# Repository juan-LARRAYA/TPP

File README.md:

# EPS CubeSat - Sistema de Gestión de Energía

Sistema de gestión de energía (EPS - Electric Power System) para CubeSat, diseñado para cumplir con las especificaciones requeridas en tensiones de salida, tasas de datos para comunicación con periféricos y vida útil extendida.

## Autores

- **Larraya, Juan Cruz** - 104162 - jlarraya@fi.uba.ar
- **Stirparo, Nicolás** - 105885 - nstirparo@fi.uba.ar
- **Paulino Alaya, Diego** - 104311 - dpaulino@fi.uba.ar

## Director y Codirectores

- **Director**: Enrique Jorge Castelli
- **Codirectores**:
  - Fernando Filippetti
  - Monica Viviana Nitoli

## Introducción

El EPS es uno de los subsistemas más críticos de un satélite, ya que de su correcto funcionamiento depende la operación continua de los demás módulos, tales como el sistema de comunicaciones, el control de actitud y el payload. Su rol principal es gestionar la energía captada por los paneles solares, regular y distribuir las tensiones necesarias, cargar las baterías y garantizar tanto la protección de las mismas como la seguridad de los circuitos asociados. Además, debe ser capaz de sensar parámetros eléctricos y térmicos para reportarlos al computador a bordo y así optimizar la eficiencia energética durante la misión.

## Motivación

Este proyecto surge de la escasa oferta de módulos EPS en Sudamérica y de los elevados costos de los productos disponibles en el mercado internacional, que en muchos casos carecen de documentación abierta para su integración. Ante esta situación, se plantea la oportunidad de desarrollar un sistema propio que no solo satisfaga las necesidades técnicas del CubeSat propuesto, sino que también contribuya al crecimiento de la industria espacial argentina mediante la generación de conocimiento y tecnología local.

## Objetivos

El proyecto entrega un **prototipo operativo** junto con:
- Documentación técnica completa
- Mediciones necesarias para su validación
- Circuito esquemático para realizar copias del circuito industrialmente a escala en un PCB bajo la norma PC104

## Características Técnicas

El sistema EPS desarrollado cuenta con las siguientes características:

### Diseño Modular
- **PPC (Power Processing and Control)**: Optimizado con control digital directo
- **BMS (Battery Management System)**: Sistema de gestión de baterías a medida
- **PDU (Power Distribution Unit)**: Unidad de distribución de energía eficiente

### Monitoreo y Sensado
- Bus I²C con sensores **INA219** para monitoreo preciso y escalable
- Medición de tensión, corriente y temperatura en puntos críticos del sistema
- Telemetría completa de parámetros eléctricos y térmicos

### Gestión Inteligente de Baterías (BMS)
- Protección integral contra sobre y baja tensión
- Protección contra sobrecorriente
- Monitoreo de temperatura
- Estado de carga (SOC)
- Capacidad de balanceo de celdas

### Cargador de Baterías con MPPT
- Extracción de máxima potencia de los paneles solares
- Algoritmo MPPT para optimización de eficiencia de carga
- Tres canales de entrada fotovoltaica independientes

### Regulación y Distribución de Energía
- Tres buses de alimentación regulados (3.3V, 5V)
- Redundancia en las salidas de 3.3V y 5V
- Limitadores de corriente en cada canal
- Compatibilidad con norma PC104

### Interfaz de Comunicación
- Comunicación UART/USART con la computadora a bordo del CubeSat
- Comandos y lectura de registros de estado de todos los módulos
- Bus I²C para sensores y periféricos

## Desarrollo del Proyecto

### Prototipo Final

### Fallos Encontrados y Soluciones Implementadas

Durante el desarrollo del proyecto se enfrentaron desafíos significativos que requirieron cambios en la metodología y arquitectura del sistema:

#### 1. Fallo Funcional del Primer Prototipo Monolítico

**Problema:** El diseño inicial, concebido como una solución "todo en uno" y fabricado profesionalmente, falló en las pruebas iniciales. Esto se debió a la complejidad inherente de un sistema monolítico, donde la interdependencia de los componentes dificulta la depuración y la identificación de la causa raíz de los fallos.

**Solución:** Se adoptó una metodología de desarrollo modular e incremental. El sistema EPS se descompuso en sus bloques funcionales principales (PPC, BMS, PDU), y cada módulo se implementó y probó de forma aislada utilizando prototipos de bajo costo. Esta estrategia permitió una depuración más controlada y económica.

#### 2. Ineficiencia en la Adquisición de Datos (Mapeo Directo por ADC)

**Problema:** El enfoque preliminar utilizaba divisores de tensión y amplificadores operacionales conectados directamente a las entradas ADC del microcontrolador. Esto resultaba en un alto consumo de pines, complejidad del circuito debido a la circuitería de acondicionamiento de señal para cada medición, y susceptibilidad al ruido en las largas pistas analógicas.

**Solución:** Se migró a una arquitectura de monitoreo digital y distribuida basada en el bus I²C, utilizando sensores de corriente y potencia INA219. Estos dispositivos integran un amplificador de precisión y un ADC de 12 bits, transmitiendo mediciones de forma digital. Esta solución redujo drásticamente el uso de pines del microcontrolador, simplificó la interconexión, aumentó la precisión y la robustez frente al ruido.

## Estructura del Repositorio

```
TPP/
├── firmware/                      # Código fuente del firmware
│   ├── TPP STM/                  # Firmware principal para STM32
│   └── demos/                    # Demostraciones y pruebas
│       ├── DuinoSTM32/          # Ejemplos con Arduino IDE para STM32
│       ├── STM32CubeIDE/        # Proyectos de STM32CubeIDE
│       ├── filmwareSTM32/       # Firmware de prueba STM32
│       └── pruebasMppt/         # Pruebas del algoritmo MPPT
│           ├── arduino/         # Versión Arduino
│           ├── esp32/           # Versión ESP32
│           └── bluePIlPrueba/   # Versión Blue Pill (STM32F103)
│
├── hardware/                      # Diseños de hardware
│   ├── PowerSis-V0.0/           # Versión inicial del diseño
│   └── kikads/                   # Diseños en KiCad
│       ├── PowerSis-V4.4+modFinales/  # Versión 4.4 con modificaciones finales
│       ├── PowerSis-V5.0/            # Versión 5.0 (última versión)
│       └── superados/                # Versiones anteriores superadas
│
├── utilidades/                    # Herramientas y scripts de utilidad
│
├── Info util CubeSat ENERGIA/    # Información y documentación de referencia
│
└── TPP Informe.pdf               # Informe técnico del proyecto
```

## ¿Qué puedes hacer con este proyecto?

### 1. Explorar el Diseño de Hardware
Navega a la carpeta `hardware/kikads/PowerSis-V5.0/` para encontrar:
- Esquemáticos del circuito completo
- Layout del PCB en formato PC104
- Lista de materiales (BOM)
- Archivos de fabricación (Gerbers)

### 2. Compilar y Cargar el Firmware
El firmware principal se encuentra en `firmware/TPP STM/`:
- Compatible con STM32
- Incluye implementación de BMS, MPPT y PDU
- Comunicación I²C y UART
- Drivers para sensores INA219

### 3. Probar Módulos Individuales
Utiliza los demos en `firmware/demos/` para:
- Probar el algoritmo MPPT de forma aislada
- Verificar la comunicación con el BQ (BMS IC)
- Testear PWM y control de conversores
- Desarrollar sobre diferentes plataformas (Arduino, ESP32, STM32)

### 4. Replicar el Sistema
Con la documentación incluida puedes:
- Fabricar tu propio PCB siguiendo el diseño PC104
- Ensamblar el sistema con la lista de materiales
- Cargar el firmware en un microcontrolador STM32
- Integrar el EPS en tu propio CubeSat

### 5. Modificar y Adaptar
El proyecto es completamente abierto para:
- Adaptar las tensiones de salida a tus necesidades
- Modificar los algoritmos de control
- Agregar nuevos sensores o funcionalidades
- Optimizar para diferentes perfiles de misión

## Documentación

- **Informe Técnico Completo**: `TPP Informe.pdf`
- **Información de Referencia**: Carpeta `Info util CubeSat ENERGIA/`
- **Esquemáticos**: `hardware/kikads/PowerSis-V5.0/`

## Requisitos

### Para el Hardware
- PCB fabricado según diseño PC104
- Componentes según BOM incluida
- Paneles solares compatibles
- Baterías LiPo/Li-Ion

### Para el Firmware
- STM32 (recomendado STM32F103 o superior)
- IDE: Arduino IDE con soporte STM32 o STM32CubeIDE
- Programador ST-Link V2 o compatible
- Sensores INA219 para telemetría

## Primeros Pasos

1. **Revisar la documentación**: Lee el informe técnico (`TPP Informe.pdf`)
2. **Explorar el hardware**: Abre los esquemáticos en KiCad desde `hardware/kikads/PowerSis-V5.0/`
3. **Compilar un demo**: Prueba el código MPPT desde `firmware/demos/pruebasMppt/`
4. **Cargar el firmware principal**: Desde `firmware/TPP STM/`

## Licencia

Este proyecto se desarrolla como Trabajo Práctico Profesional de la Facultad de Ingeniería - UBA, con el objetivo de contribuir al desarrollo de la tecnología espacial argentina.

## Contacto

Para consultas sobre el proyecto, contactar a los autores a través de sus correos electrónicos listados arriba.

---

**Universidad de Buenos Aires - Facultad de Ingeniería**
*Trabajo Práctico Profesional - 2024*

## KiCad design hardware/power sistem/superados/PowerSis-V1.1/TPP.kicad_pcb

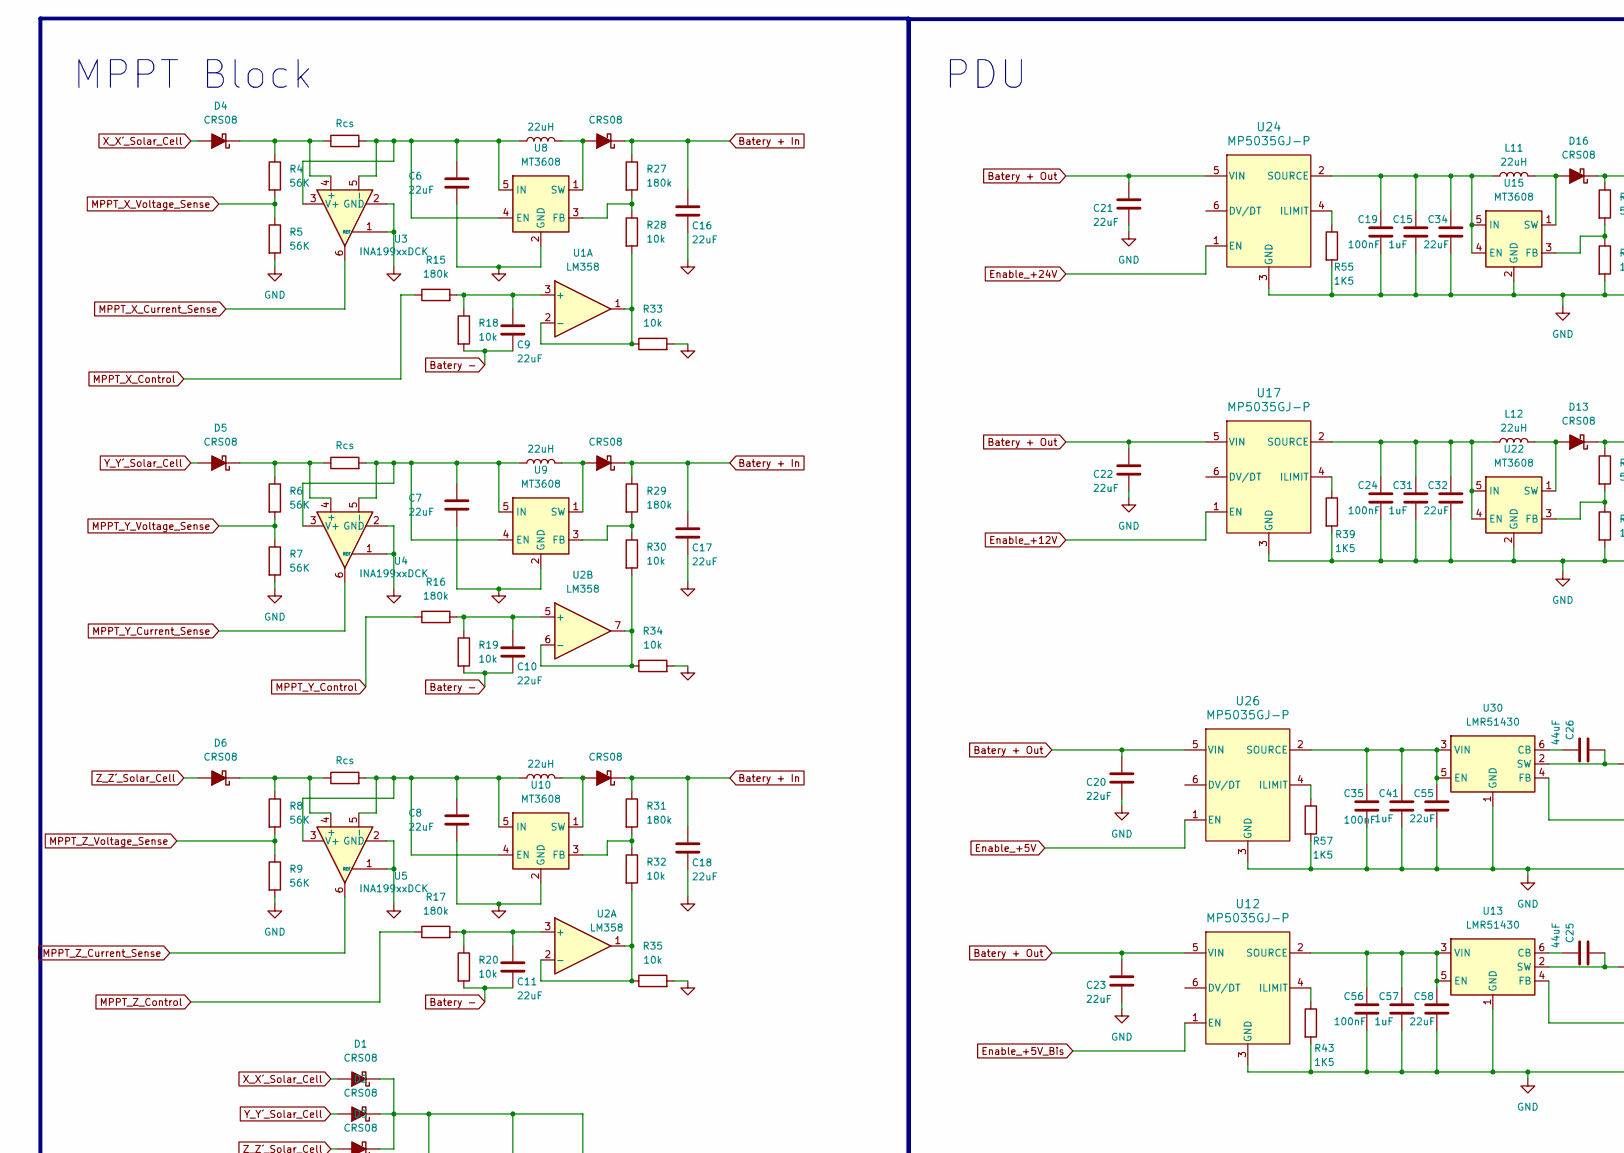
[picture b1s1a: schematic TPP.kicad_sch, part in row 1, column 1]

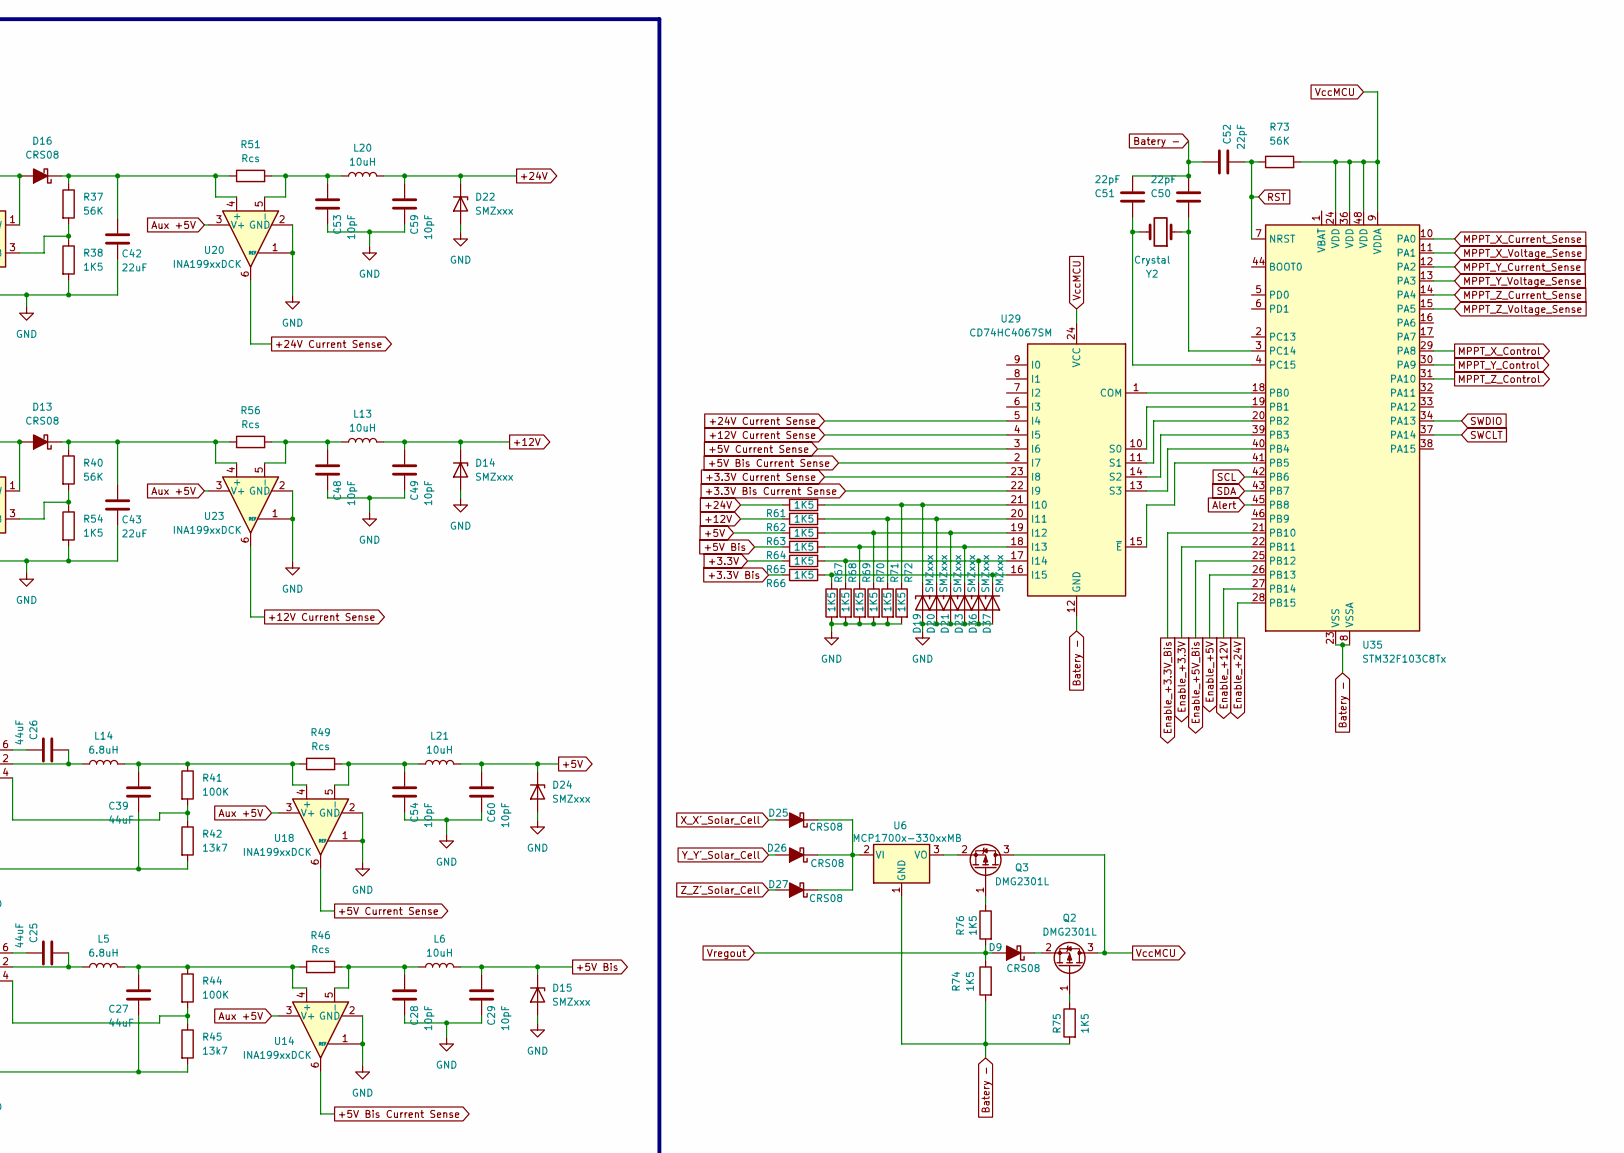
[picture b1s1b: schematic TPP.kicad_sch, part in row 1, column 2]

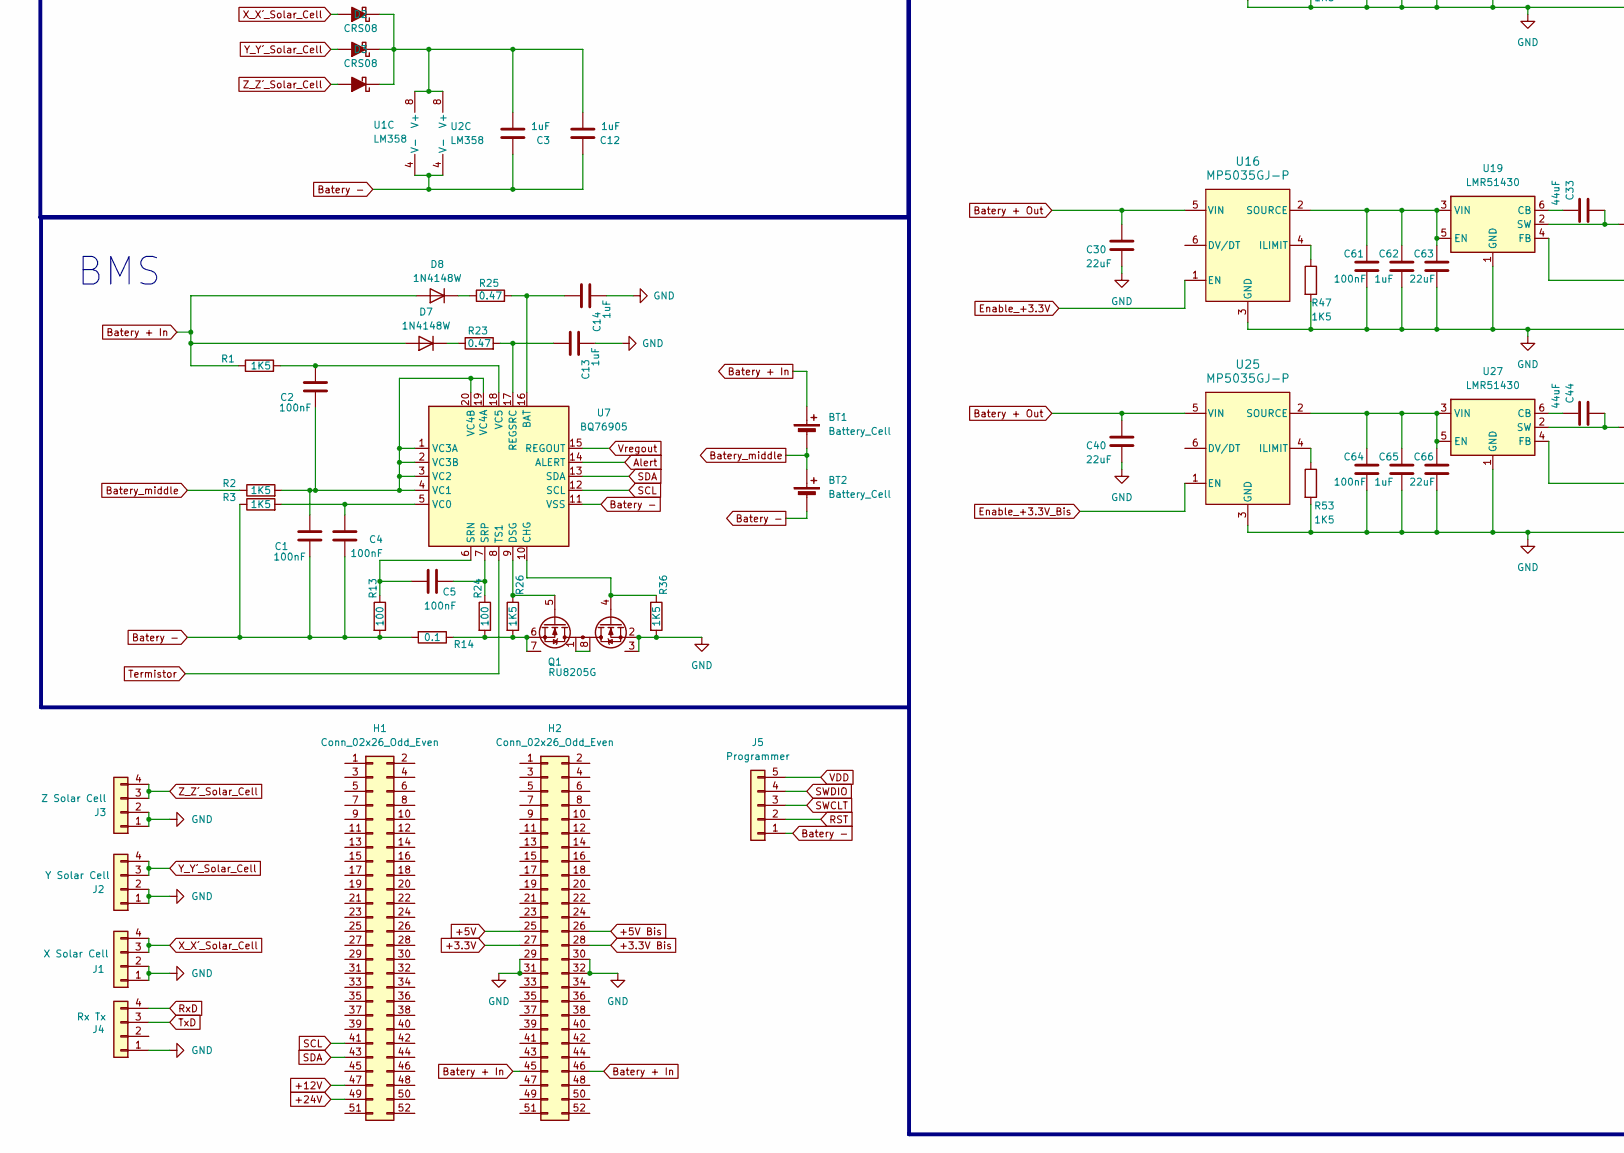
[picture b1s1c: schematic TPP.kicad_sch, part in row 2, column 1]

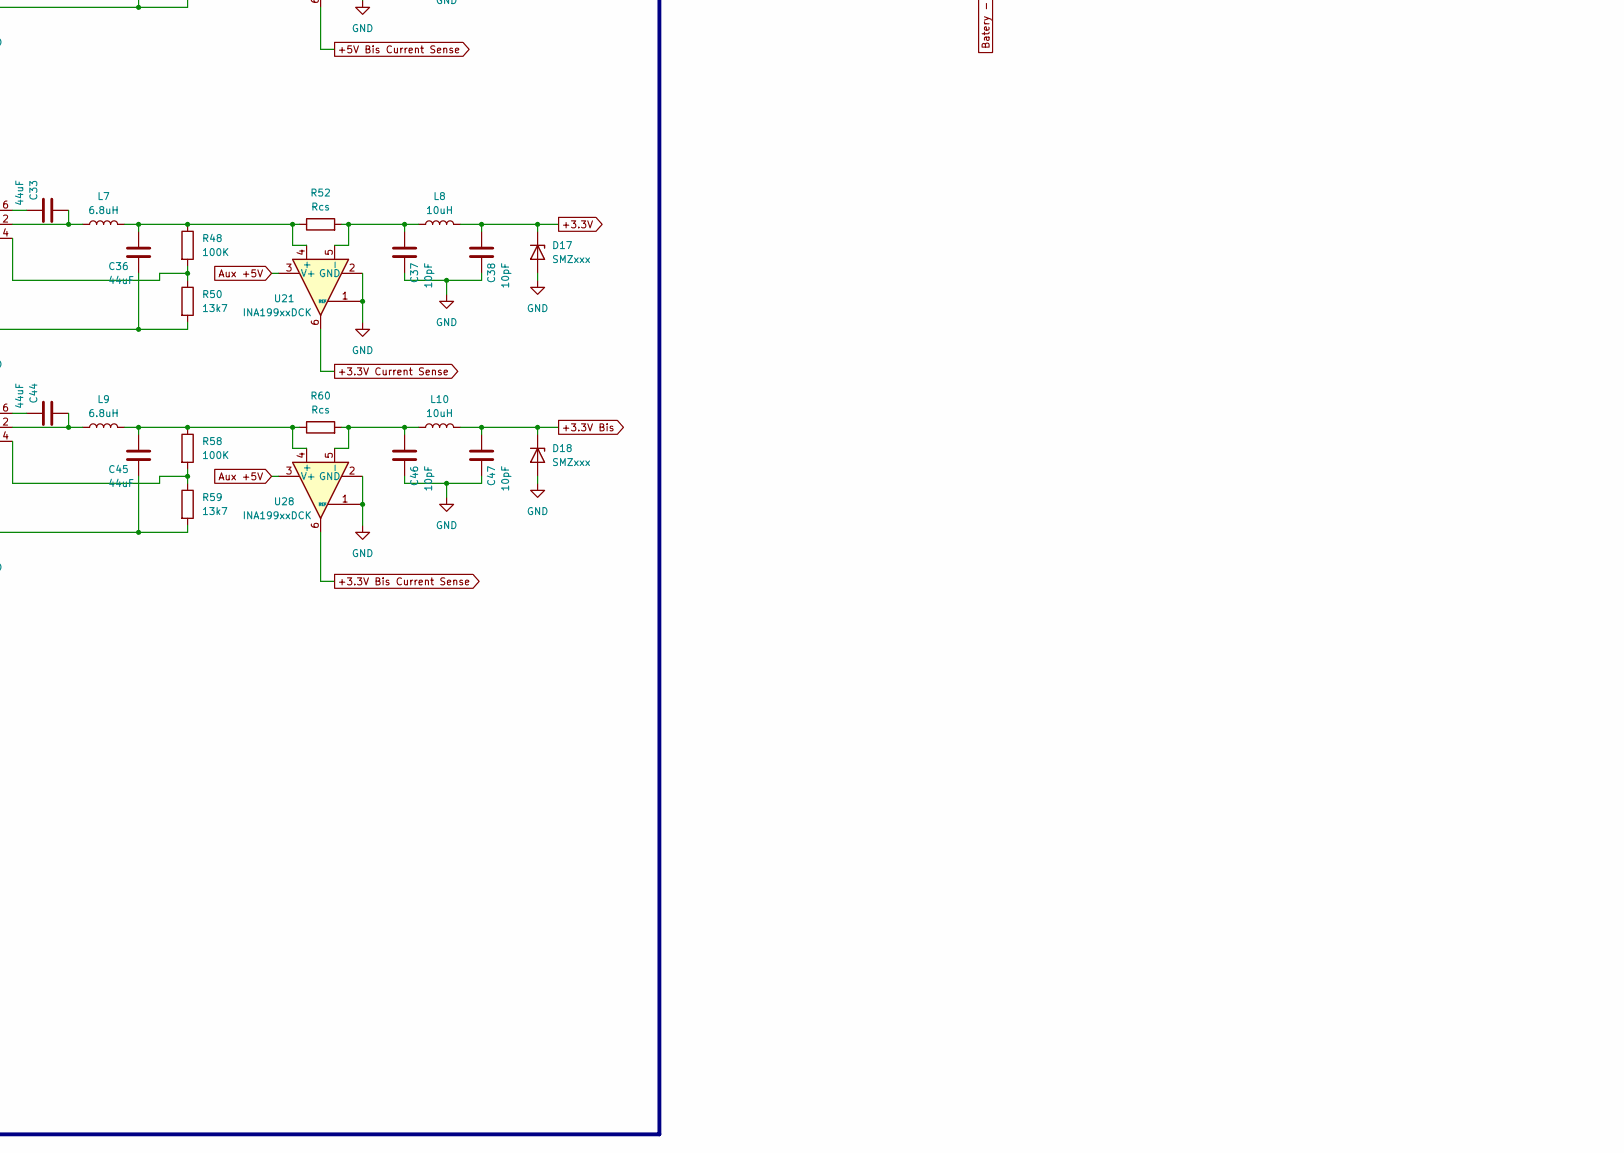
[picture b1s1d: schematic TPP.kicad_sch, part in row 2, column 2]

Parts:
BT1, BT2: Battery_Cell; BatteryHolder_MPD_BH-18650-PC2
C1, C2, C4, C5, C19, C24, C35, C56, C61, C64: 100nF; C_0603_1608Metric_Pad1.08x0.95mm_HandSolder
C3, C12, C13, C14, C15, C31, C41, C57, C62, C65: 1uF; C_0603_1608Metric_Pad1.08x0.95mm_HandSolder
C6, C7, C8, C9, C10, C11, C16, C17, C18, C20, C21, C22, C23, C30, C32, C34, C40, C42, C43, C55, C58, C63, C66: 22uF; C_0603_1608Metric_Pad1.08x0.95mm_HandSolder
C25, C26, C27, C33, C36, C39, C44, C45: 44uF; C_0603_1608Metric_Pad1.08x0.95mm_HandSolder
C28, C29, C37, C38, C46, C47, C48, C49, C53, C54, C59, C60: 10pF; C_0603_1608Metric_Pad1.08x0.95mm_HandSolder
C50, C51, C52: 22pF; C_0603_1608Metric_Pad1.08x0.95mm_HandSolder
D1, D2, D3, D4, D5, D6, D9, D10, D11, D12, D13, D16, D25, D26, D27: CRS08; D_SMA
D7, D8: 1N4148W; D_SOD-123
D14, D15, D17, D18, D19, D20, D21, D22, D23, D24, D36, D37: SMZxxx; D_MELF
H1, H2: Conn_02x26_Odd_Even; PinSocket_2x26_P2.54mm_Vertical
J1: X Solar Cell; JST_XH_S4B-XH-A-1_1x04_P2.50mm_Horizontal
J2: Y Solar Cell; JST_XH_S4B-XH-A-1_1x04_P2.50mm_Horizontal
J3: Z Solar Cell; JST_XH_S4B-XH-A-1_1x04_P2.50mm_Horizontal
J4: Rx Tx; JST_XH_S4B-XH-A-1_1x04_P2.50mm_Horizontal
J5: Programmer; PinHeader_1x05_P2.54mm_Vertical
L2, L3, L4, L11, L12: 22uH; L_Abracon_ASPI-0630LR
L5, L7, L9, L14: 6.8uH; L_Abracon_ASPI-0630LR
L6, L8, L10, L13, L20, L21: 10uH; L_Abracon_ASPI-0630LR
Q1: RU8205G; TSSOP-8_4.4x3mm_P0.65mm
Q2, Q3: DMG2301L; SOT-23
R1, R2, R3, R26, R36, R38, R39, R43, R47, R53, R54, R55, R57, R61, R62, R63, R64, R65, R66, R67, R68, R69, R70, R71, R72, R74, R75, R76: 1K5; R_0805_2012Metric_Pad1.20x1.40mm_HandSolder
R4, R5, R6, R7, R8, R9, R37, R40, R73: 56K; R_0805_2012Metric_Pad1.20x1.40mm_HandSolder
R10, R11, R12, R46, R49, R51, R52, R56, R60: Rcs; R_0805_2012Metric_Pad1.20x1.40mm_HandSolder
R13, R24: 100; R_0805_2012Metric_Pad1.20x1.40mm_HandSolder
R14: 0.1; R_0805_2012Metric_Pad1.20x1.40mm_HandSolder
R15, R16, R17, R27, R29, R31: 180k; R_0805_2012Metric_Pad1.20x1.40mm_HandSolder
R18, R19, R20, R28, R30, R32, R33, R34, R35: 10k; R_0805_2012Metric_Pad1.20x1.40mm_HandSolder
R23, R25: 0.47; R_0805_2012Metric_Pad1.20x1.40mm_HandSolder
R41, R44, R48, R58: 100K; R_0805_2012Metric_Pad1.20x1.40mm_HandSolder
R42, R45, R50, R59: 13k7; R_0805_2012Metric_Pad1.20x1.40mm_HandSolder
U1: LM358; SOIC-8_3.9x4.9mm_P1.27mm
U2: LM358
U3, U4, U5, U14, U18, U20, U21, U23, U28: INA199xxDCK; SOT-363_SC-70-6
U6: MCP1700x-330xxMB; SOT-89-3
U7: BQ76905; QFN-20-1EP_3x3mm_P0.4mm_EP1.65x1.65mm_ThermalVias
U8, U9, U10, U15, U22: MT3608; SOT-23-6
U12, U16, U17, U24, U25, U26: MP5035GJ-P; TSOT-23-6_HandSoldering
U13, U19, U27, U30: LMR51430; SOT-23-6
U29: CD74HC4067SM; SSOP-24_5.3x8.2mm_P0.65mm
U35: STM32F103C8Tx; LQFP-48_7x7mm_P0.5mm
Y2: Crystal; Crystal_HC49-U_Vertical

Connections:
+3.3V: C38.2, D17.1 (K), H2.27, L8.2
+3.3V: R65.1
+3.3V Bis: R66.1
+3.3V Bis: C47.2, D18.1 (K), H2.28, L10.2
+3.3V Bis Current Sense: U28.6, U29.22 (I9)
+3.3V Current Sense: U21.6, U29.23 (I8)
+5V: C60.2, D24.1 (K), H2.25, L21.2, R63.1
+5V Bis: C29.2, D15.1 (K), H2.26, L6.2, R64.1
+5V Bis Current Sense: U14.6, U29.2 (I7)
+5V Current Sense: U18.6, U29.3 (I6)
+12V: C49.2, D14.1 (K), H1.47, L13.2, R62.1
+12V Current Sense: U23.6, U29.4 (I5)
+24V: C59.2, D22.1 (K), H1.49, L20.2, R61.1
+24V Current Sense: U20.6, U29.5 (I4)
Alert: U7.14 (ALERT), U35.45 (PB8)
Aux +5V: U14.3 (V+), U18.3 (V+), U20.3 (V+), U21.3 (V+), U23.3 (V+), U28.3 (V+)
Batery + In: BT1.1 (+), C16.1, C17.1, C18.1, D7.2 (A), D8.2 (A), D10.1 (K), D11.1 (K), D12.1 (K), H2.45, H2.46, R1.1, R27.1, R29.1, R31.1
Batery + Out: C20.1, C21.1, C22.1, C23.1, C30.1, C40.1, U12.5 (VIN), U16.5 (VIN), U17.5 (VIN), U24.5 (VIN), U25.5 (VIN), U26.5 (VIN)
Batery -: BT2.2 (-), C1.1, C3.1, C4.1, C9.2, C10.2, C11.2, C12.1, C50.1, C51.1, C52.2, J5.1, R3.1, R13.2, R14.2, R18.2, R19.2, R20.2, R74.2, R75.2, U1.4 (V-), U2.4 (V-), U6.1 (GND), U7.11 (VSS), U29.12 (GND), U35.8 (VSSA), U35.23 (VSS), U35.35 (VSS), U35.47 (VSS)
Batery_middle: BT1.2 (-), BT2.1 (+), R2.1
Enable_+3.3V: U16.1 (EN), U35.22 (PB11)
Enable_+3.3V_Bis: U25.1 (EN), U35.21 (PB10)
Enable_+5V: U26.1 (EN), U35.26 (PB13)
Enable_+5V_Bis: U12.1 (EN), U35.25 (PB12)
Enable_+12V: U17.1 (EN), U35.27 (PB14)
Enable_+24V: U24.1 (EN), U35.28 (PB15)
GND: C6.2, C7.2, C8.2, C13.1, C14.1, C15.2, C16.2, C17.2, C18.2, C19.2, C20.2, C21.2, C22.2, C23.2, C24.2, C27.2, C28.1, C29.1, C30.2, C31.2, C32.2, C34.2, C35.2, C36.2, C37.1, C38.1, C39.2, C40.2, C41.2, C42.2, C43.2, C45.2, C46.1, C47.1, C48.1, C49.1, C53.1, C54.1, C55.2, C56.2, C57.2, C58.2, C59.1, C60.1, C61.2, C62.2, C63.2, C64.2, C65.2, C66.2, D14.2 (A), D15.2 (A), D17.2 (A), D18.2 (A), D19.2 (A), D20.2 (A), D21.2 (A), D22.2 (A), D23.2 (A), D24.2 (A), D36.2 (A), D37.2 (A), H2.29, H2.30, H2.31, H2.32, J1.1, J1.2, J2.1, J2.2, J3.1, J3.2, J4.1, Q1.2 (D1), Q1.3 (D1), R5.2, R7.2, R9.2, R33.2, R34.2, R35.2, R36.2, R38.2, R39.2, R42.2, R43.2, R45.2, R47.2, R50.2, R53.2, R54.2, R55.2, R57.2, R59.2, R67.2, R68.2, R69.2, R70.2, R71.2, R72.2, U3.1 (REF), U3.2 (GND), U4.1 (REF), U4.2 (GND), U5.1 (REF), U5.2 (GND), U8.2 (GND), U9.2 (GND), U10.2 (GND), U12.3 (GND), U13.1 (GND), U14.1 (REF), U14.2 (GND), U15.2 (GND), U16.3 (GND), U17.3 (GND), U18.1 (REF), U18.2 (GND), U19.1 (GND), U20.1 (REF), U20.2 (GND), U21.1 (REF), U21.2 (GND), U22.2 (GND), U23.1 (REF), U23.2 (GND), U24.3 (GND), U25.3 (GND), U26.3 (GND), U27.1 (GND), U28.1 (REF), U28.2 (GND), U30.1 (GND)
MPPT_X_Control: R15.1, U35.29 (PA8)
MPPT_X_Current_Sense: U3.6, U35.10 (PA0)
MPPT_X_Voltage_Sense: R4.2, R5.1, U35.11 (PA1)
MPPT_Y_Control: R16.1, U35.30 (PA9)
MPPT_Y_Current_Sense: U4.6, U35.12 (PA2)
MPPT_Y_Voltage_Sense: R6.2, R7.1, U35.13 (PA3)
MPPT_Z_Control: R17.1, U35.31 (PA10)
MPPT_Z_Current_Sense: U5.6, U35.14 (PA4)
MPPT_Z_Voltage_Sense: R8.2, R9.1, U35.15 (PA5)
unnamed: C3.2, C12.2, D1.1 (K), D2.1 (K), D3.1 (K), U1.8 (V+), U2.8 (V+)
unnamed: D4.1 (K), R4.1, R10.1, U3.4 (+)
unnamed: D5.1 (K), R6.1, R11.1, U4.4 (+)
unnamed: D6.1 (K), R8.1, R12.1, U5.4 (+)
unnamed: D7.1 (K), R23.1
unnamed: D8.1 (K), R25.1
unnamed: D9.1 (K), Q2.2 (S)
unnamed: D10.2 (A), L2.2, U8.1 (SW)
unnamed: D11.2 (A), L3.2, U9.1 (SW)
unnamed: D12.2 (A), L4.2, U10.1 (SW)
unnamed: D13.2 (A), L12.2, U22.1 (SW)
unnamed: C43.1, D13.1 (K), R40.1, R56.1, U23.4 (+)
unnamed: D16.2 (A), L11.2, U15.1 (SW)
unnamed: C42.1, D16.1 (K), R37.1, R51.1, U20.4 (+)
unnamed: D19.1 (K), R61.2, R72.1, U29.21 (I10)
unnamed: D20.1 (K), R62.2, R71.1, U29.20 (I11)
unnamed: D21.1 (K), R63.2, R70.1, U29.19 (I12)
unnamed: D23.1 (K), R64.2, R69.1, U29.18 (I13)
unnamed: D25.1 (K), D26.1 (K), D27.1 (K), U6.2 (VI)
unnamed: D36.1 (K), R65.2, R68.1, U29.17 (I14)
unnamed: D37.1 (K), R66.2, R67.1, U29.16 (I15)
unnamed: Q1.4 (G1), R36.1, U7.10 (CHG)
unnamed: Q1.5 (G2), R26.1, U7.9 (DSG)
unnamed: Q1.1 (S1/D2), Q1.8 (S1/D2)
unnamed: Q1.6 (S2), Q1.7 (S2), R14.1, R24.2, R26.2
unnamed: Q2.1 (G), R75.1
unnamed: Q3.1 (G), R76.1
unnamed: Q3.2 (S), U6.3 (VO)
unnamed: C9.1, R15.2, R18.1, U1.3 (+)
unnamed: R28.2, R33.1, U1.1, U1.2 (-)
unnamed: C11.1, R17.2, R20.1, U2.3 (+)
unnamed: R32.2, R35.1, U2.1, U2.2 (-)
unnamed: C10.1, R16.2, R19.1, U2.5 (+)
unnamed: R30.2, R34.1, U2.6 (-), U2.7
unnamed: C6.1, L2.1, R10.2, U3.3 (V+), U3.5 (-), U8.4 (EN), U8.5 (IN)
unnamed: C7.1, L3.1, R11.2, U4.3 (V+), U4.5 (-), U9.4 (EN), U9.5 (IN)
unnamed: C14.2, R25.2, U7.16 (BAT)
unnamed: C13.2, R23.2, U7.17 (REGSRC)
unnamed: C5.1, R13.1, U7.6 (SRN)
unnamed: C5.2, R24.1, U7.7 (SRP)
unnamed: C4.2, R3.2, U7.5 (VC0)
unnamed: C1.2, C2.1, R2.2, U7.1 (VC3A), U7.2 (VC3B), U7.3 (VC2), U7.4 (VC1), U7.19 (VC4A), U7.20 (VC4B)
unnamed: C2.2, R1.2, U7.18 (VC5)
unnamed: R27.2, R28.1, U8.3 (FB)
unnamed: R29.2, R30.1, U9.3 (FB)
unnamed: C8.1, L4.1, R12.2, U5.3 (V+), U5.5 (-), U10.4 (EN), U10.5 (IN)
unnamed: R31.2, R32.1, U10.3 (FB)
unnamed: R43.1, U12.4 (ILIMIT)
unnamed: C56.1, C57.1, C58.1, U12.2 (SOURCE), U13.3 (VIN), U13.5 (EN)
unnamed: C25.2, U13.6 (CB)
unnamed: R44.2, R45.1, U13.4 (FB)
unnamed: C25.1, L5.1, U13.2 (SW)
unnamed: C27.1, L5.2, R44.1, R46.1, U14.4 (+)
unnamed: C28.2, L6.1, R46.2, U14.5 (-)
unnamed: C15.1, C19.1, C34.1, L11.1, U15.4 (EN), U15.5 (IN), U24.2 (SOURCE)
unnamed: R37.2, R38.1, U15.3 (FB)
unnamed: R47.1, U16.4 (ILIMIT)
unnamed: C61.1, C62.1, C63.1, U16.2 (SOURCE), U19.3 (VIN), U19.5 (EN)
unnamed: R39.1, U17.4 (ILIMIT)
unnamed: C24.1, C31.1, C32.1, L12.1, U17.2 (SOURCE), U22.4 (EN), U22.5 (IN)
unnamed: C39.1, L14.2, R41.1, R49.1, U18.4 (+)
unnamed: C54.2, L21.1, R49.2, U18.5 (-)
unnamed: C33.2, U19.6 (CB)
unnamed: R48.2, R50.1, U19.4 (FB)
unnamed: C33.1, L7.1, U19.2 (SW)
unnamed: C53.2, L20.1, R51.2, U20.5 (-)
unnamed: C36.1, L7.2, R48.1, R52.1, U21.4 (+)
unnamed: C37.2, L8.1, R52.2, U21.5 (-)
unnamed: R40.2, R54.1, U22.3 (FB)
unnamed: C48.2, L13.1, R56.2, U23.5 (-)
unnamed: R55.1, U24.4 (ILIMIT)
unnamed: R53.1, U25.4 (ILIMIT)
unnamed: C64.1, C65.1, C66.1, U25.2 (SOURCE), U27.3 (VIN), U27.5 (EN)
unnamed: R57.1, U26.4 (ILIMIT)
unnamed: C35.1, C41.1, C55.1, U26.2 (SOURCE), U30.3 (VIN), U30.5 (EN)
unnamed: C44.2, U27.6 (CB)
unnamed: R58.2, R59.1, U27.4 (FB)
unnamed: C44.1, L9.1, U27.2 (SW)
unnamed: C45.1, L9.2, R58.1, R60.1, U28.4 (+)
unnamed: C46.2, L10.1, R60.2, U28.5 (-)
unnamed: U29.1 (COM), U35.18 (PB0)
unnamed: U29.10 (S0), U35.19 (PB1)
unnamed: U29.11 (S1), U35.20 (PB2)
unnamed: U29.14 (S2), U35.39 (PB3)
unnamed: U29.13 (S3), U35.40 (PB4)
unnamed: U29.15 (~E), U35.41 (PB5)
unnamed: C26.2, U30.6 (CB)
unnamed: R41.2, R42.1, U30.4 (FB)
unnamed: C26.1, L14.1, U30.2 (SW)
unnamed: C50.2, U35.3 (PC14), Y2.1
unnamed: C51.2, U35.4 (PC15), Y2.2
RST: C52.1, J5.2, R73.1, U35.7 (NRST)
RxD: J4.4
SCL: H1.41, U7.12 (SCL), U35.42 (PB6)
SDA: H1.43, U7.13 (SDA), U35.43 (PB7)
SWCLT: J5.3, U35.37 (PA14)
SWDIO: J5.4, U35.34 (PA13)
Termistor: U7.8 (TS1)
TxD: J4.3
VDD: J5.5
VccMCU: Q2.3 (D), Q3.3 (D), R73.2, U29.24 (VCC), U35.9 (VDDA), U35.24 (VDD), U35.36 (VDD), U35.48 (VDD)
Vregout: D9.2 (A), R74.1, R76.2, U7.15 (REGOUT)
X_X´_Solar_Cell: D1.2 (A), D4.2 (A), D25.2 (A), J1.3, J1.4
Y_Y´_Solar_Cell: D2.2 (A), D5.2 (A), D26.2 (A), J2.3, J2.4
Z_Z´_Solar_Cell: D3.2 (A), D6.2 (A), D27.2 (A), J3.3, J3.4

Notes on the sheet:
BMS
PDU
MPPT Block

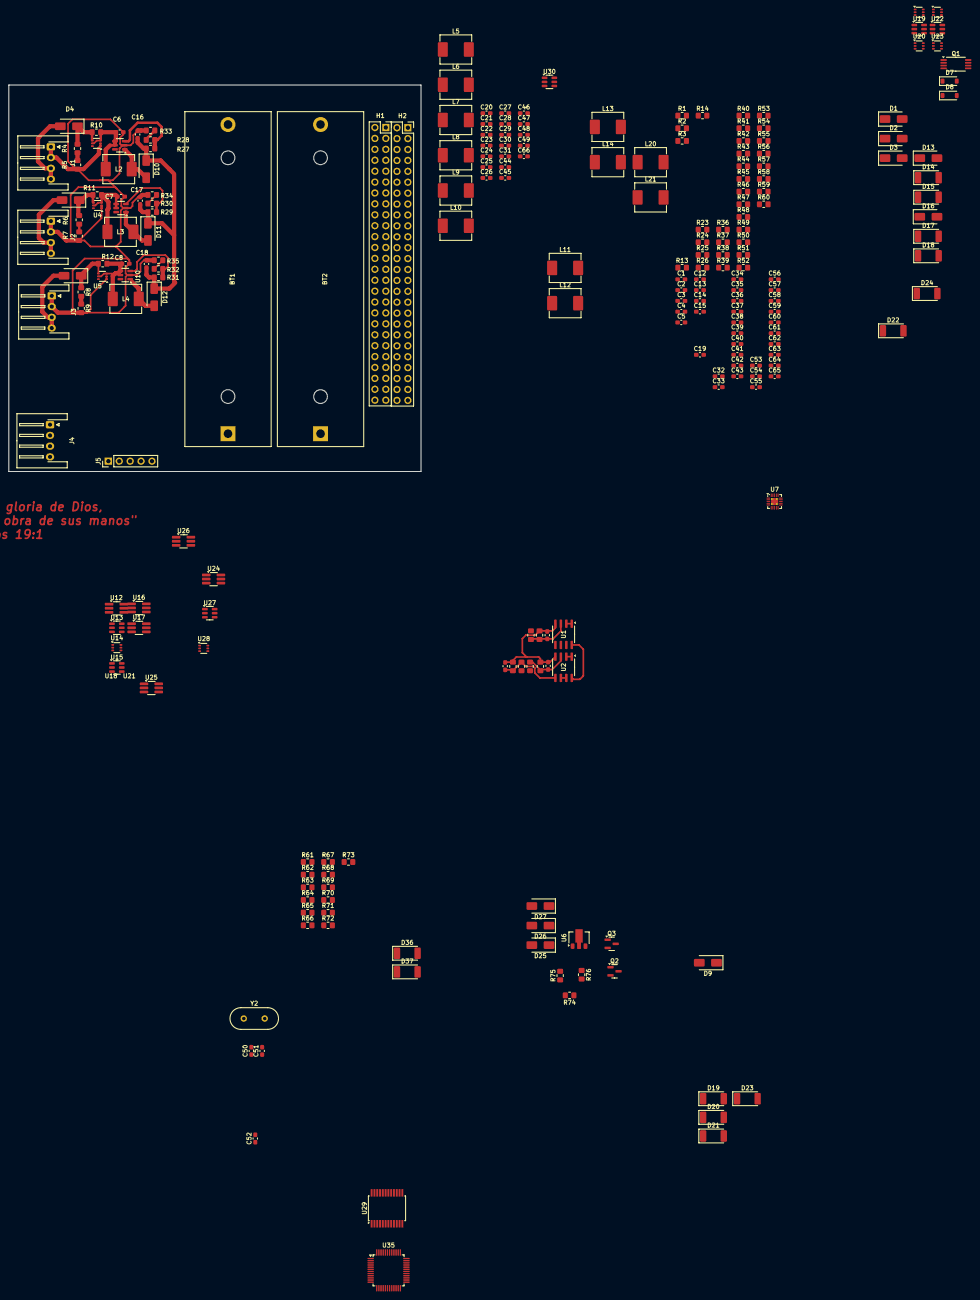
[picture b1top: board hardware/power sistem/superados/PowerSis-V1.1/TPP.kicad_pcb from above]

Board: 2 copper layers, 96.0 x 90.0 mm, 227 parts (0 on the bottom side), 135 nets.
